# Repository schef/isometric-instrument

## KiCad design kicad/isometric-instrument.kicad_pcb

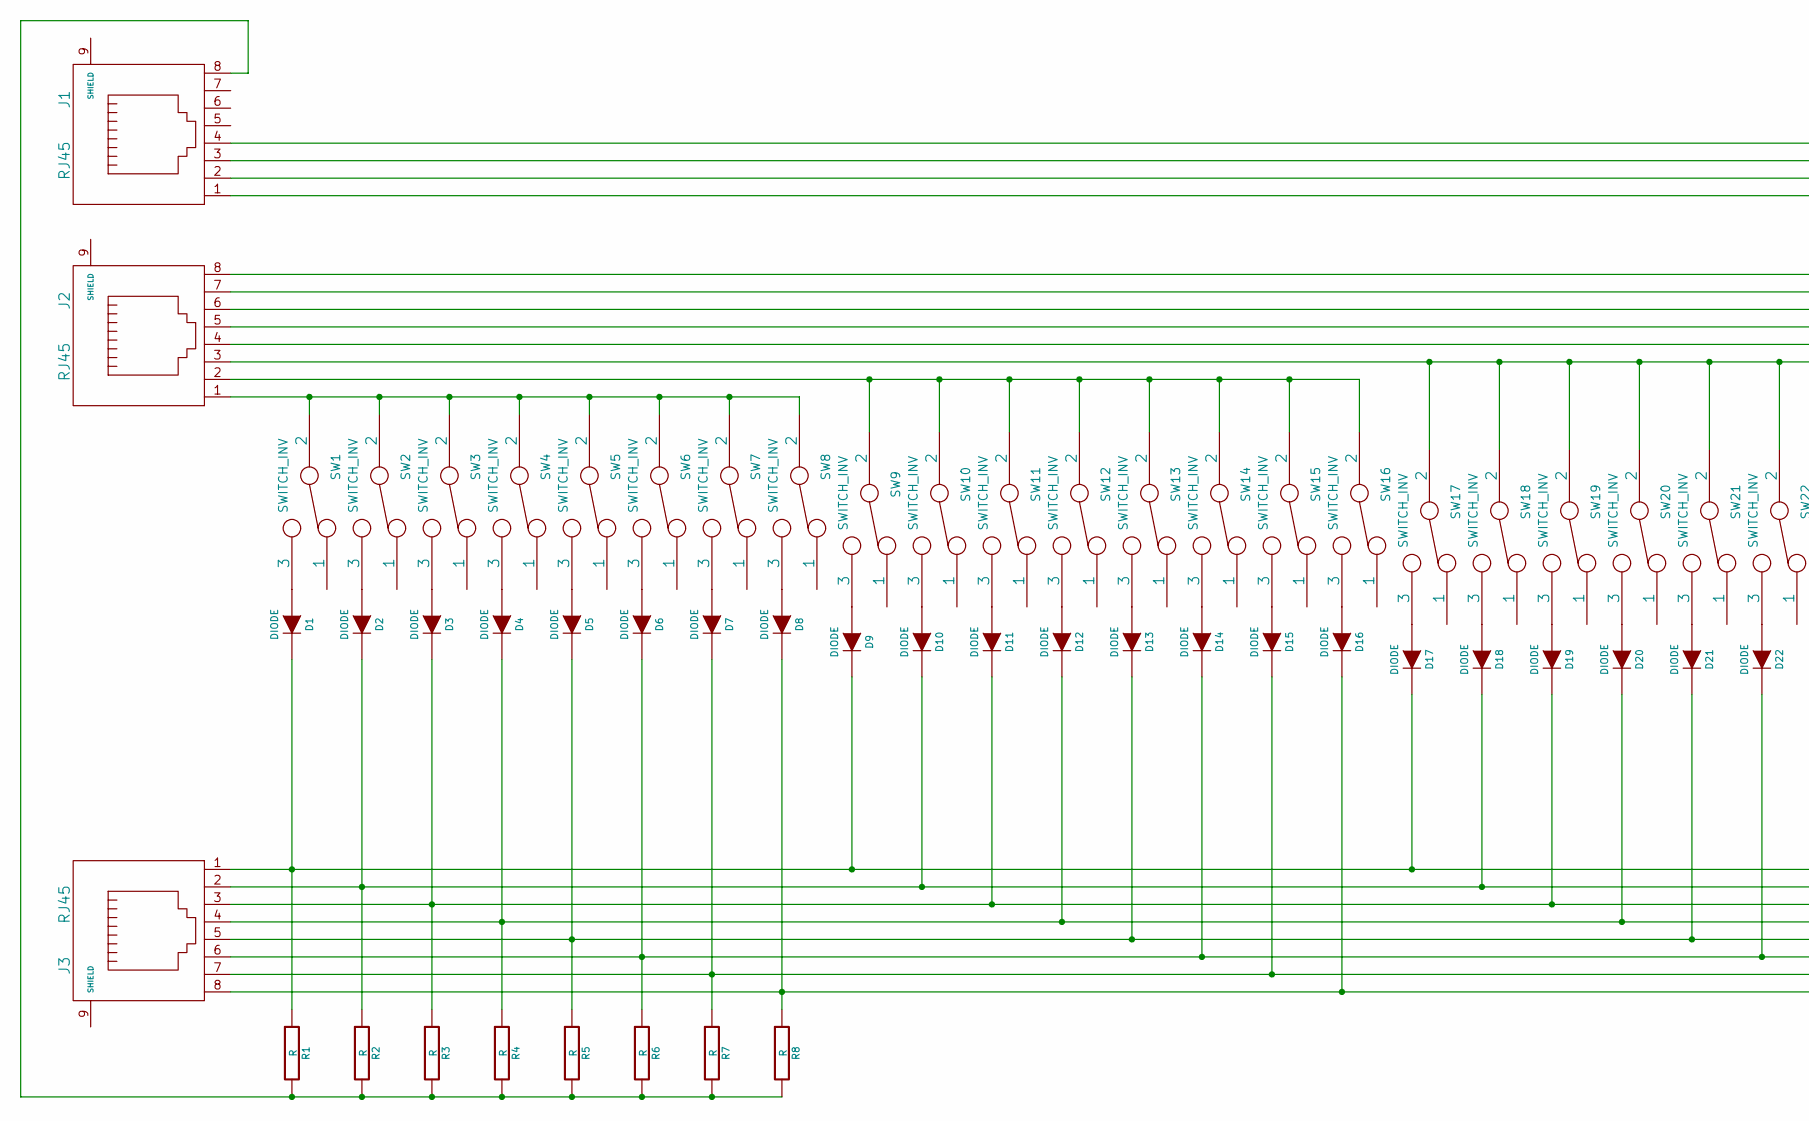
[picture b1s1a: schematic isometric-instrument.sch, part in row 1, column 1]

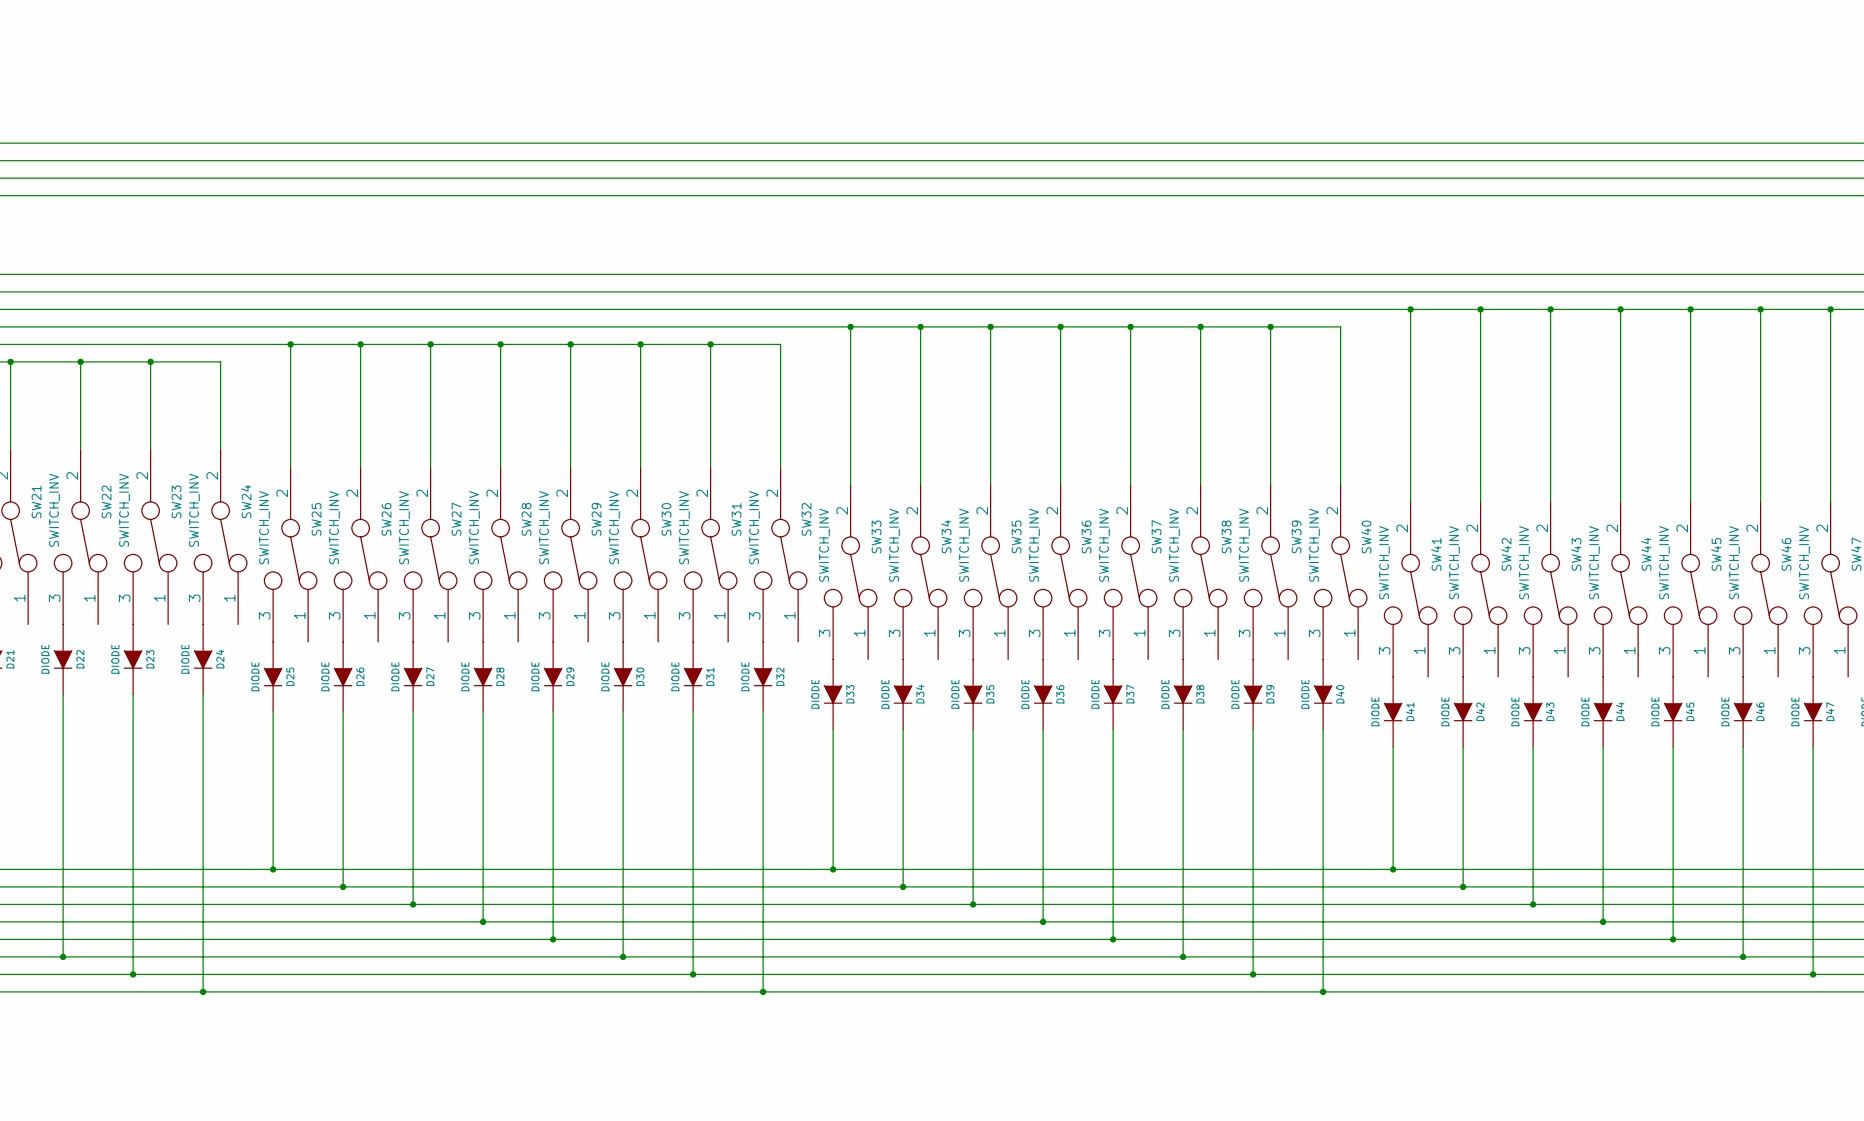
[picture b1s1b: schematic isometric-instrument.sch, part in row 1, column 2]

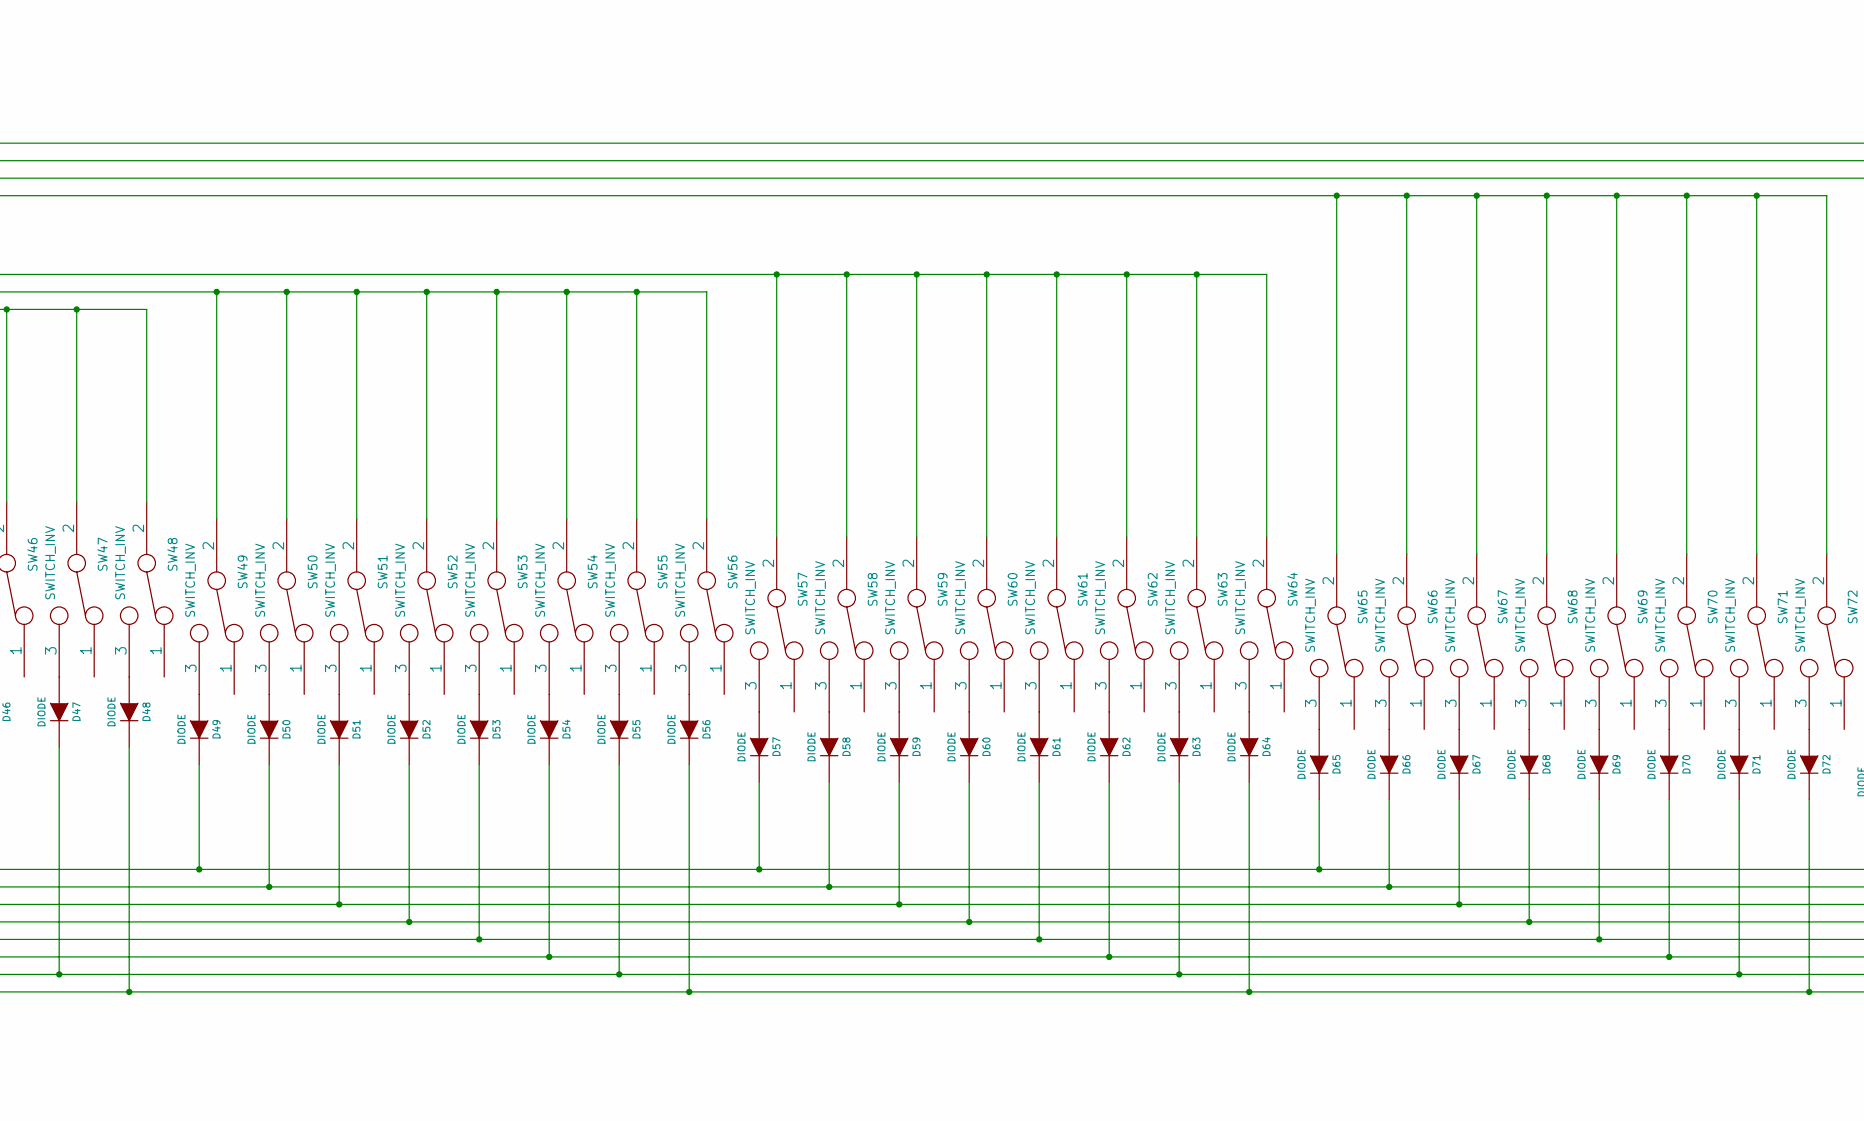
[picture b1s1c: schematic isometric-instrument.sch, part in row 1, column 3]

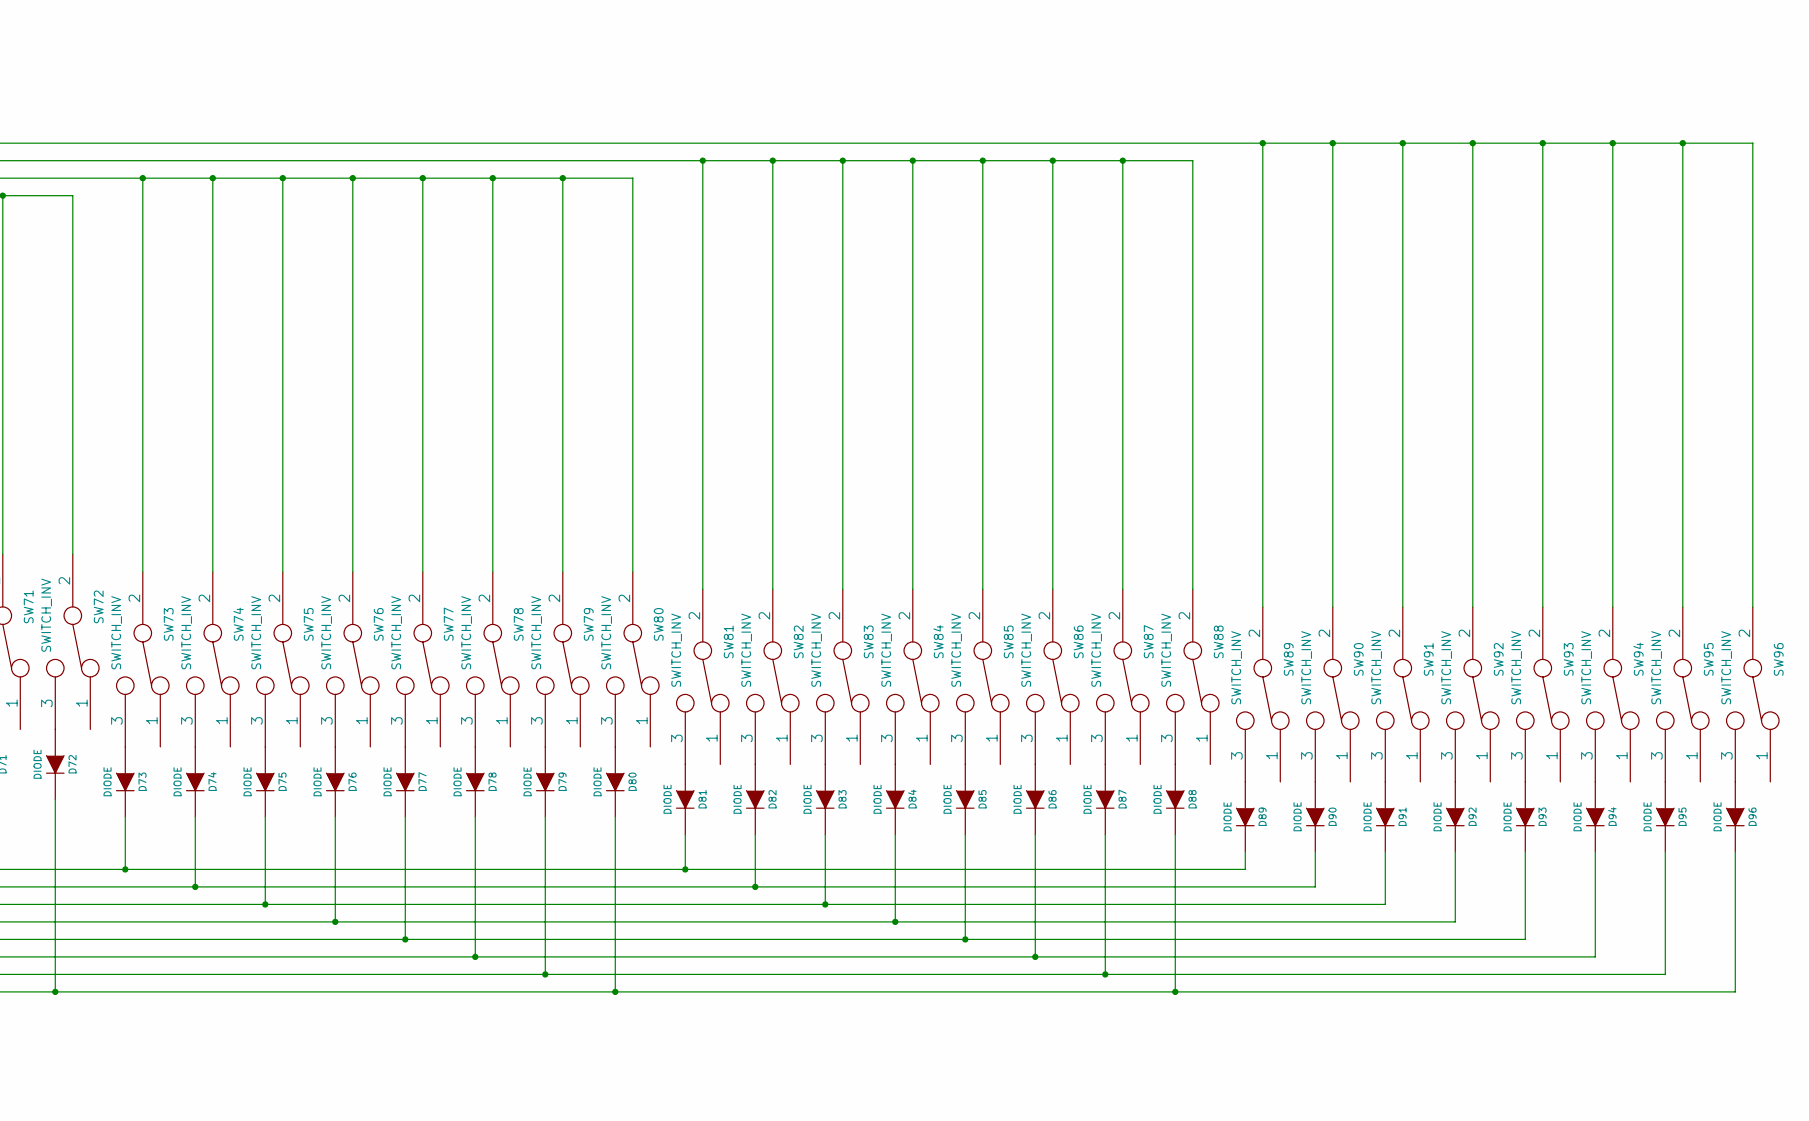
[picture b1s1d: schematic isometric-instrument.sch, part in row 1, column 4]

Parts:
D1, D2, D3, D4, D5, D6, D7, D8, D9, D10, D11, D12, D13, D14, D15, D16, D17, D18, D19, D20, D21, D22, D23, D24, D25, D26, D27, D28, D29, D30, D31, D32, D33, D34, D35, D36, D37, D38, D39, D40, D41, D42, D43, D44, D45, D46, D47, D48, D49, D50, D51, D52, D53, D54, D55, D56, D57, D58, D59, D60, D61, D62, D63, D64, D65, D66, D67, D68, D69, D70, D71, D72, D73, D74, D75, D76, D77, D78, D79, D80, D81, D82, D83, D84, D85, D86, D87, D88, D89, D90, D91, D92, D93, D94, D95, D96: DIODE; Diode_DO-41_SOD81_Horizontal_RM10
J1, J2, J3: RJ45; RJ45_8
R1, R2, R3, R4, R5, R6, R7, R8: R; Resistor_Horizontal_RM10mm
SW1, SW2, SW3, SW4, SW5, SW6, SW7, SW8, SW9, SW10, SW11, SW12, SW13, SW14, SW15, SW16, SW17, SW18, SW19, SW20, SW21, SW22, SW23, SW24, SW25, SW26, SW27, SW28, SW29, SW30, SW31, SW32, SW33, SW34, SW35, SW36, SW37, SW38, SW39, SW40, SW41, SW42, SW43, SW44, SW45, SW46, SW47, SW48, SW49, SW50, SW51, SW52, SW53, SW54, SW55, SW56, SW57, SW58, SW59, SW60, SW61, SW62, SW63, SW64, SW65, SW66, SW67, SW68, SW69, SW70, SW71, SW72, SW73, SW74, SW75, SW76, SW77, SW78, SW79, SW80, SW81, SW82, SW83, SW84, SW85, SW86, SW87, SW88, SW89, SW90, SW91, SW92, SW93, SW94, SW95, SW96: SWITCH_INV; microswitch_5_08mm

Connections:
unnamed: D1.1 (A), SW1.3
unnamed: D1.2 (K), D9.2 (K), D17.2 (K), D25.2 (K), D33.2 (K), D41.2 (K), D49.2 (K), D57.2 (K), D65.2 (K), D73.2 (K), D81.2 (K), D89.2 (K), J3.1, R1.1
unnamed: D2.1 (A), SW2.3
unnamed: D3.1 (A), SW3.3
unnamed: D4.1 (A), SW4.3
unnamed: D5.1 (A), SW5.3
unnamed: D6.1 (A), SW6.3
unnamed: D7.1 (A), SW7.3
unnamed: D8.1 (A), SW8.3
unnamed: D9.1 (A), SW9.3
unnamed: D10.1 (A), SW10.3
unnamed: D2.2 (K), D10.2 (K), D18.2 (K), D26.2 (K), D34.2 (K), D42.2 (K), D50.2 (K), D58.2 (K), D66.2 (K), D74.2 (K), D82.2 (K), D90.2 (K), J3.2, R2.1
unnamed: D11.1 (A), SW11.3
unnamed: D3.2 (K), D11.2 (K), D19.2 (K), D27.2 (K), D35.2 (K), D43.2 (K), D51.2 (K), D59.2 (K), D67.2 (K), D75.2 (K), D83.2 (K), D91.2 (K), J3.3, R3.1
unnamed: D12.1 (A), SW12.3
unnamed: D4.2 (K), D12.2 (K), D20.2 (K), D28.2 (K), D36.2 (K), D44.2 (K), D52.2 (K), D60.2 (K), D68.2 (K), D76.2 (K), D84.2 (K), D92.2 (K), J3.4, R4.1
unnamed: D13.1 (A), SW13.3
unnamed: D5.2 (K), D13.2 (K), D21.2 (K), D29.2 (K), D37.2 (K), D45.2 (K), D53.2 (K), D61.2 (K), D69.2 (K), D77.2 (K), D85.2 (K), D93.2 (K), J3.5, R5.1
unnamed: D14.1 (A), SW14.3
unnamed: D6.2 (K), D14.2 (K), D22.2 (K), D30.2 (K), D38.2 (K), D46.2 (K), D54.2 (K), D62.2 (K), D70.2 (K), D78.2 (K), D86.2 (K), D94.2 (K), J3.6, R6.1
unnamed: D15.1 (A), SW15.3
unnamed: D7.2 (K), D15.2 (K), D23.2 (K), D31.2 (K), D39.2 (K), D47.2 (K), D55.2 (K), D63.2 (K), D71.2 (K), D79.2 (K), D87.2 (K), D95.2 (K), J3.7, R7.1
unnamed: D16.1 (A), SW16.3
unnamed: D8.2 (K), D16.2 (K), D24.2 (K), D32.2 (K), D40.2 (K), D48.2 (K), D56.2 (K), D64.2 (K), D72.2 (K), D80.2 (K), D88.2 (K), D96.2 (K), J3.8, R8.1
unnamed: D17.1 (A), SW17.3
unnamed: D18.1 (A), SW18.3
unnamed: D19.1 (A), SW19.3
unnamed: D20.1 (A), SW20.3
unnamed: D21.1 (A), SW21.3
unnamed: D22.1 (A), SW22.3
unnamed: D23.1 (A), SW23.3
unnamed: D24.1 (A), SW24.3
unnamed: D25.1 (A), SW25.3
unnamed: D26.1 (A), SW26.3
unnamed: D27.1 (A), SW27.3
unnamed: D28.1 (A), SW28.3
unnamed: D29.1 (A), SW29.3
unnamed: D30.1 (A), SW30.3
unnamed: D31.1 (A), SW31.3
unnamed: D32.1 (A), SW32.3
unnamed: D33.1 (A), SW33.3
unnamed: D34.1 (A), SW34.3
unnamed: D35.1 (A), SW35.3
unnamed: D36.1 (A), SW36.3
unnamed: D37.1 (A), SW37.3
unnamed: D38.1 (A), SW38.3
unnamed: D39.1 (A), SW39.3
unnamed: D40.1 (A), SW40.3
unnamed: D41.1 (A), SW41.3
unnamed: D42.1 (A), SW42.3
unnamed: D43.1 (A), SW43.3
unnamed: D44.1 (A), SW44.3
unnamed: D45.1 (A), SW45.3
unnamed: D46.1 (A), SW46.3
unnamed: D47.1 (A), SW47.3
unnamed: D48.1 (A), SW48.3
unnamed: D49.1 (A), SW49.3
unnamed: D50.1 (A), SW50.3
unnamed: D51.1 (A), SW51.3
unnamed: D52.1 (A), SW52.3
unnamed: D53.1 (A), SW53.3
unnamed: D54.1 (A), SW54.3
unnamed: D55.1 (A), SW55.3
unnamed: D56.1 (A), SW56.3
unnamed: D57.1 (A), SW57.3
unnamed: D58.1 (A), SW58.3
unnamed: D59.1 (A), SW59.3
unnamed: D60.1 (A), SW60.3
unnamed: D61.1 (A), SW61.3
unnamed: D62.1 (A), SW62.3
unnamed: D63.1 (A), SW63.3
unnamed: D64.1 (A), SW64.3
unnamed: D65.1 (A), SW65.3
unnamed: D66.1 (A), SW66.3
unnamed: D67.1 (A), SW67.3
unnamed: D68.1 (A), SW68.3
unnamed: D69.1 (A), SW69.3
unnamed: D70.1 (A), SW70.3
unnamed: D71.1 (A), SW71.3
unnamed: D72.1 (A), SW72.3
unnamed: D73.1 (A), SW73.3
unnamed: D74.1 (A), SW74.3
unnamed: D75.1 (A), SW75.3
unnamed: D76.1 (A), SW76.3
unnamed: D77.1 (A), SW77.3
unnamed: D78.1 (A), SW78.3
unnamed: D79.1 (A), SW79.3
unnamed: D80.1 (A), SW80.3
unnamed: D81.1 (A), SW81.3
unnamed: D82.1 (A), SW82.3
unnamed: D83.1 (A), SW83.3
unnamed: D84.1 (A), SW84.3
unnamed: D85.1 (A), SW85.3
unnamed: D86.1 (A), SW86.3
unnamed: D87.1 (A), SW87.3
unnamed: D88.1 (A), SW88.3
unnamed: D89.1 (A), SW89.3
unnamed: D90.1 (A), SW90.3
unnamed: D91.1 (A), SW91.3
unnamed: D92.1 (A), SW92.3
unnamed: D93.1 (A), SW93.3
unnamed: D94.1 (A), SW94.3
unnamed: D95.1 (A), SW95.3
unnamed: D96.1 (A), SW96.3
unnamed: J1.1, SW65.2, SW66.2, SW67.2, SW68.2, SW69.2, SW70.2, SW71.2, SW72.2
unnamed: J1.2, SW73.2, SW74.2, SW75.2, SW76.2, SW77.2, SW78.2, SW79.2, SW80.2
unnamed: J1.3, SW81.2, SW82.2, SW83.2, SW84.2, SW85.2, SW86.2, SW87.2, SW88.2
unnamed: J1.4, SW89.2, SW90.2, SW91.2, SW92.2, SW93.2, SW94.2, SW95.2, SW96.2
unnamed: J1.8, R1.2, R2.2, R3.2, R4.2, R5.2, R6.2, R7.2, R8.2
unnamed: J2.1, SW1.2, SW2.2, SW3.2, SW4.2, SW5.2, SW6.2, SW7.2, SW8.2
unnamed: J2.2, SW9.2, SW10.2, SW11.2, SW12.2, SW13.2, SW14.2, SW15.2, SW16.2
unnamed: J2.3, SW17.2, SW18.2, SW19.2, SW20.2, SW21.2, SW22.2, SW23.2, SW24.2
unnamed: J2.4, SW25.2, SW26.2, SW27.2, SW28.2, SW29.2, SW30.2, SW31.2, SW32.2
unnamed: J2.5, SW33.2, SW34.2, SW35.2, SW36.2, SW37.2, SW38.2, SW39.2, SW40.2
unnamed: J2.6, SW41.2, SW42.2, SW43.2, SW44.2, SW45.2, SW46.2, SW47.2, SW48.2
unnamed: J2.7, SW49.2, SW50.2, SW51.2, SW52.2, SW53.2, SW54.2, SW55.2, SW56.2
unnamed: J2.8, SW57.2, SW58.2, SW59.2, SW60.2, SW61.2, SW62.2, SW63.2, SW64.2

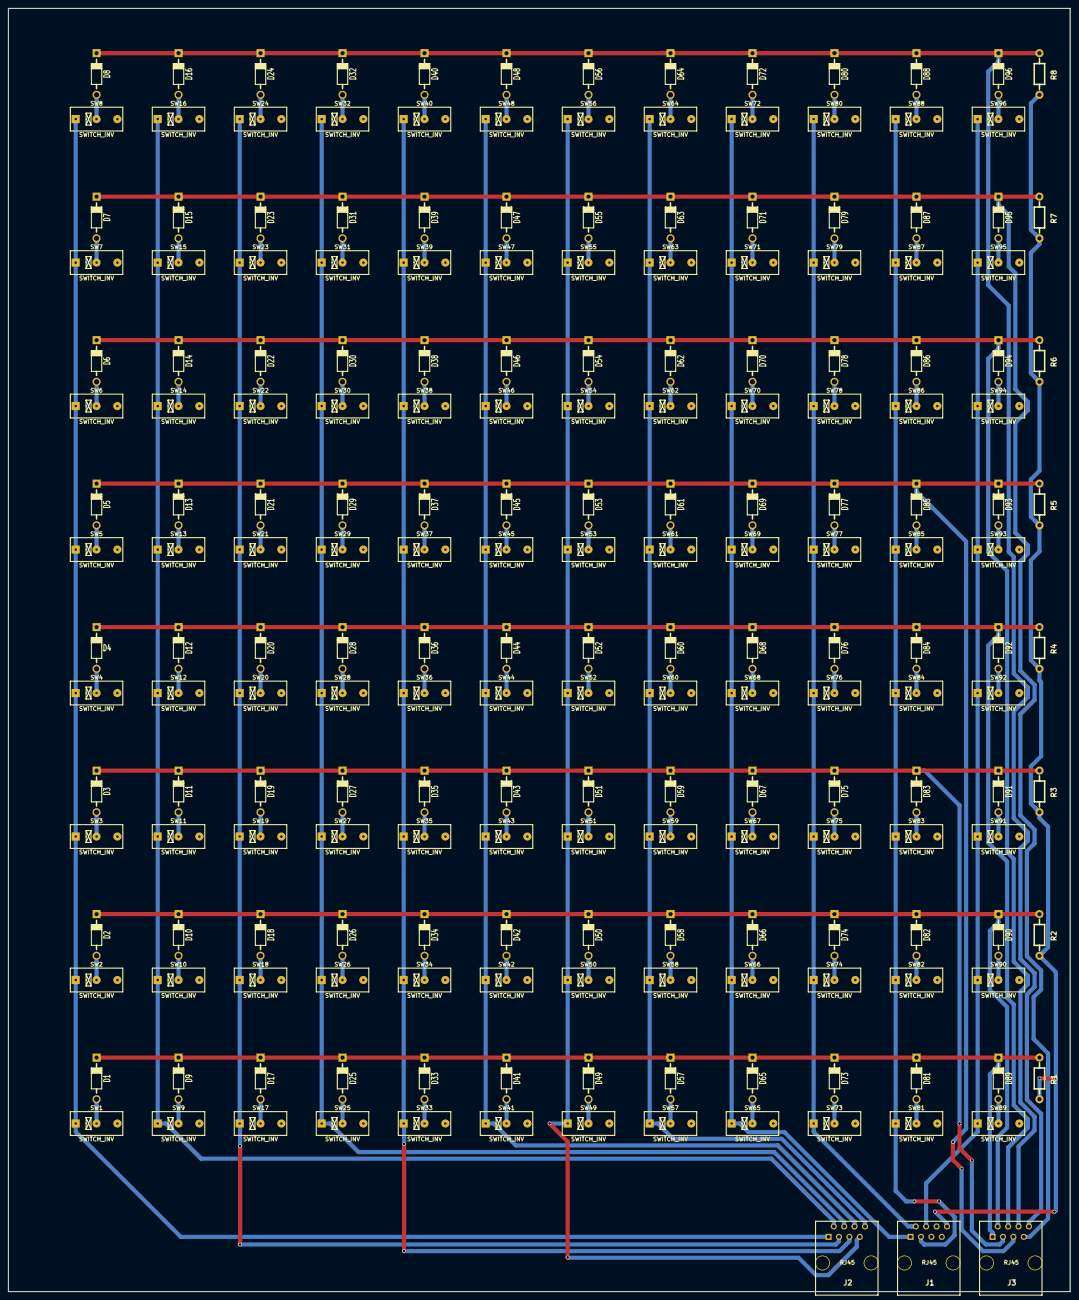
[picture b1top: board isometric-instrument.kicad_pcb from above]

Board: 2 copper layers, 259.0 x 313.0 mm, 203 parts (0 on the bottom side), 117 nets.

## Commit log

2014-09-30 inicijalni test
2014-09-30 tocne rupe
2014-10-24 za pcb
2014-10-24 kicad fileovi
2014-11-01 rezi van
2014-11-03 gotovo
2014-11-03 edge novi .dxf
2014-11-07 backup
2015-06-27 promjena oktave na rubovima
